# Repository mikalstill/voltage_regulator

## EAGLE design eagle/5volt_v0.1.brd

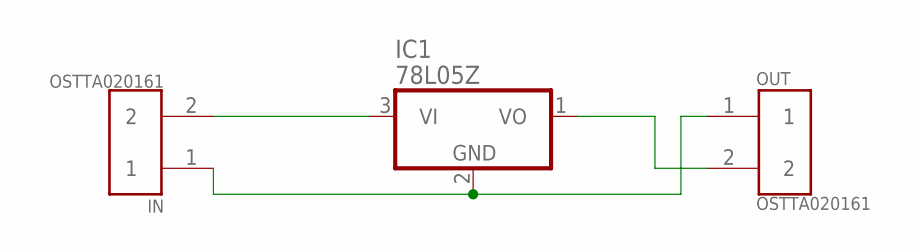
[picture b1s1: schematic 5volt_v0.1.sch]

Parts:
IC1: 78L05Z; TO92
IN: OSTTA020161; OST_OSTTA020161
OUT: OSTTA020161; OST_OSTTA020161

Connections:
unnamed: IC1.3 (VI), IN.2
unnamed: IC1.1 (VO), OUT.2
unnamed: IC1.2 (GND), IN.1, OUT.1

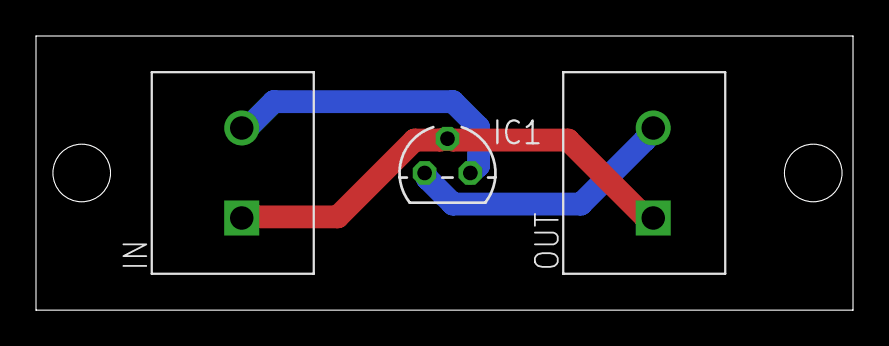
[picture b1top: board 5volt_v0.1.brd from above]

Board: 2 copper layers, 45.4 x 15.2 mm, 3 parts (0 on the bottom side), 3 nets.
